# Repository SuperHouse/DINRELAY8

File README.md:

DIN-Mount 8-Channel Relay Output
================================
Copyright 2017-2018 SuperHouse Automation Pty Ltd  www.superhouse.tv  

8-channel relay board designed for switching mains loads in a
switchboard. Fits inside a H8456 DIN-rail mounted case.

Includes a switchmode power supply with 5V output. Controls for the
relays are provided on an I/O Breakout header (12-pin IDC) compatible
with other I/O Breakout boards from SuperHouse.

More information is available at:

  http://www.superhouse.tv/dinrelay8

INSTALLATION
------------
The design is saved as an EAGLE project. EAGLE PCB design software is
available from www.cadsoftusa.com free for non-commercial use. To use
this project download it and place the directory containing these files
into the "eagle" directory on your computer. Then open EAGLE and
navigate to the project.

DISTRIBUTION
------------
The specific terms of distribution of this project are governed by the
license referenced below.

LICENSE
-------
Licensed under the TAPR Open Hardware License (www.tapr.org/OHL).
The "license" folder within this repository also contains a copy of
this license in plain text format.

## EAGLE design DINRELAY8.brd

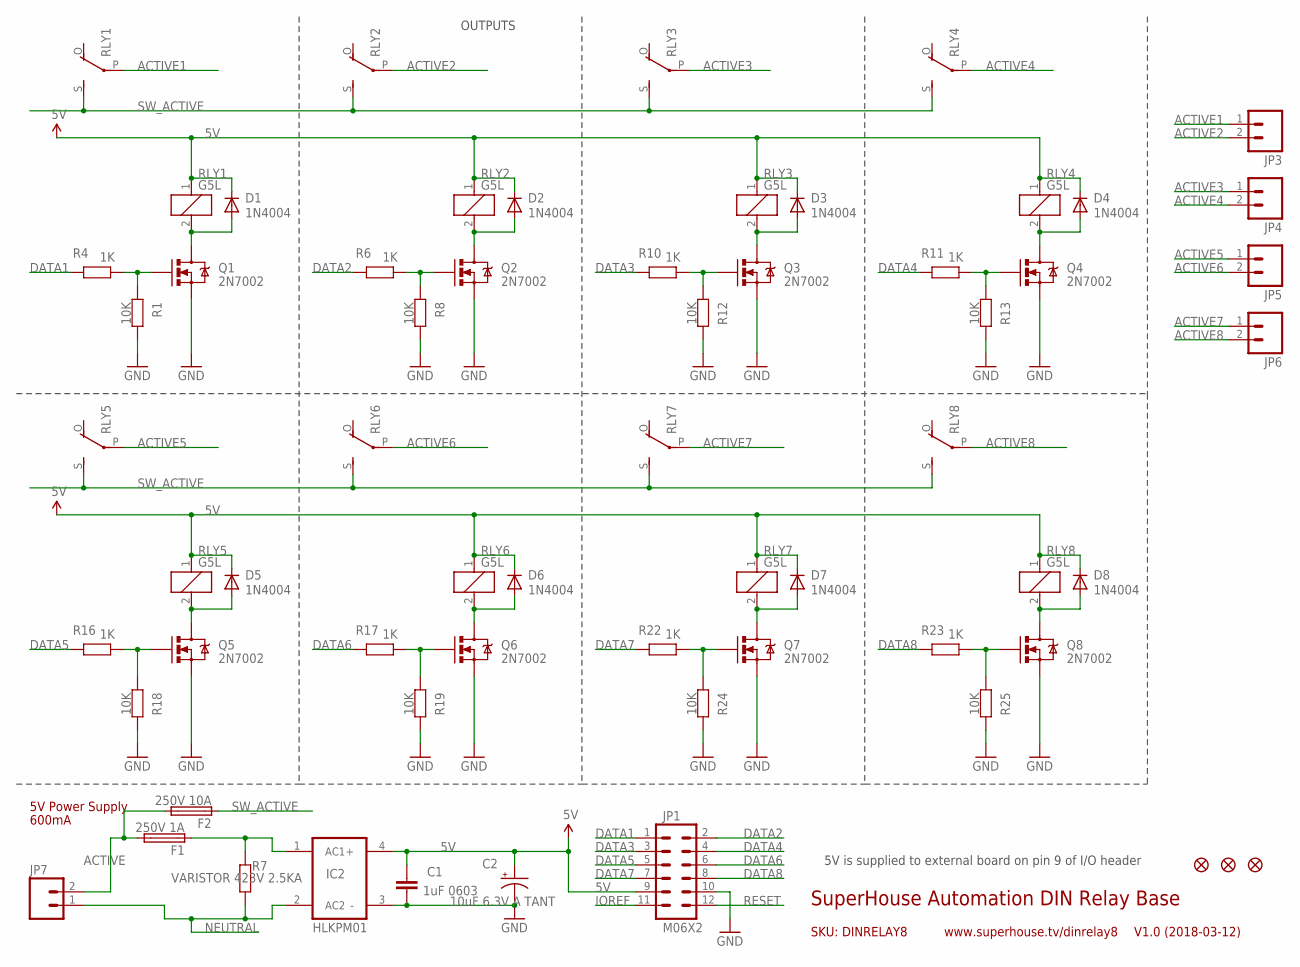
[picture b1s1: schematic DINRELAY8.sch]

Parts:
C1: 1uF 0603; 0603@1
C2: 10uF 6.3V A TANT; EIA3216
D1, D2, D3, D4, D5, D6, D7, D8: 1N4004; SMB-DIODE
F1: 250V 1A; PICOFUSE
F2: 250V 10A; PICOFUSE
FID1, FID2, FID3: FIDUCIAL1X2.5; FIDUCIAL-1X2.5
IC2: HLKPM01
JP1: M06X2; 2X6-SHROUDED
JP3, JP4, JP5, JP6, JP7: M025MM; SCREWTERMINAL-5MM-2
Q1, Q2, Q3, Q4, Q5, Q6, Q7, Q8: 2N7002; SOT23-3
R1, R8, R12, R13, R18, R19, R24, R25: 10K; 0603
R4, R6, R10, R11, R16, R17, R22, R23: 1K; 0603
R7: VARISTOR 423V 2.5KA; AXIAL-0.3
RLY1, RLY2, RLY3, RLY4, RLY5, RLY6, RLY7, RLY8: G5L; G5LE

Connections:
5V: C1.1, C2.A (+), D1.C, D2.C, D3.C, D4.C, D5.C, D6.C, D7.C, D8.C, IC2.4 (+), JP1.9, RLY1.1, RLY2.1, RLY3.1, RLY4.1, RLY5.1, RLY6.1, RLY7.1, RLY8.1
$N16: F1.1, IC2.1 (AC1), R7.P$2 (2)
ACTIVE: F1.2, F2.2, JP7.2
ACTIVE1: JP3.1, RLY1.P
ACTIVE2: JP3.2, RLY2.P
ACTIVE3: JP4.1, RLY3.P
ACTIVE4: JP4.2, RLY4.P
ACTIVE5: JP5.1, RLY5.P
ACTIVE6: JP5.2, RLY6.P
ACTIVE7: JP6.1, RLY7.P
ACTIVE8: JP6.2, RLY8.P
DATA1: JP1.1, R4.2
DATA2: JP1.2, R6.2
DATA3: JP1.3, R10.2
DATA4: JP1.4, R11.2
DATA5: JP1.5, R16.2
DATA6: JP1.6, R17.2
DATA7: JP1.7, R22.2
DATA8: JP1.8, R23.2
GND: C1.2, C2.C (-), IC2.3 (-), JP1.10, Q1.2 (S), Q2.2 (S), Q3.2 (S), Q4.2 (S), Q5.2 (S), Q6.2 (S), Q7.2 (S), Q8.2 (S), R1.2, R8.2, R12.2, R13.2, R18.2, R19.2, R24.2, R25.2
IOREF: JP1.11
unnamed: D2.A, Q2.3 (D), RLY2.2
unnamed: D1.A, Q1.3 (D), RLY1.2
unnamed: Q1.1 (G), R1.1, R4.1
unnamed: Q2.1 (G), R6.1, R8.1
unnamed: D4.A, Q4.3 (D), RLY4.2
unnamed: D3.A, Q3.3 (D), RLY3.2
unnamed: Q3.1 (G), R10.1, R12.1
unnamed: Q4.1 (G), R11.1, R13.1
unnamed: D6.A, Q6.3 (D), RLY6.2
unnamed: D5.A, Q5.3 (D), RLY5.2
unnamed: Q5.1 (G), R16.1, R18.1
unnamed: Q6.1 (G), R17.1, R19.1
unnamed: D8.A, Q8.3 (D), RLY8.2
unnamed: D7.A, Q7.3 (D), RLY7.2
unnamed: Q7.1 (G), R22.1, R24.1
unnamed: Q8.1 (G), R23.1, R25.1
NEUTRAL: IC2.2 (AC2), JP7.1, R7.P$1 (1)
RESET: JP1.12
SW_ACTIVE: F2.1, RLY1.S, RLY2.S, RLY3.S, RLY4.S, RLY5.S, RLY6.S, RLY7.S, RLY8.S

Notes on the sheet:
SKU: DINRELAY8
5V Power Supply
600mA
SuperHouse Automation DIN Relay Base
V1.0 (2018-03-12)
www.superhouse.tv/dinrelay8
OUTPUTS
5V is supplied to external board on pin 9 of I/O header

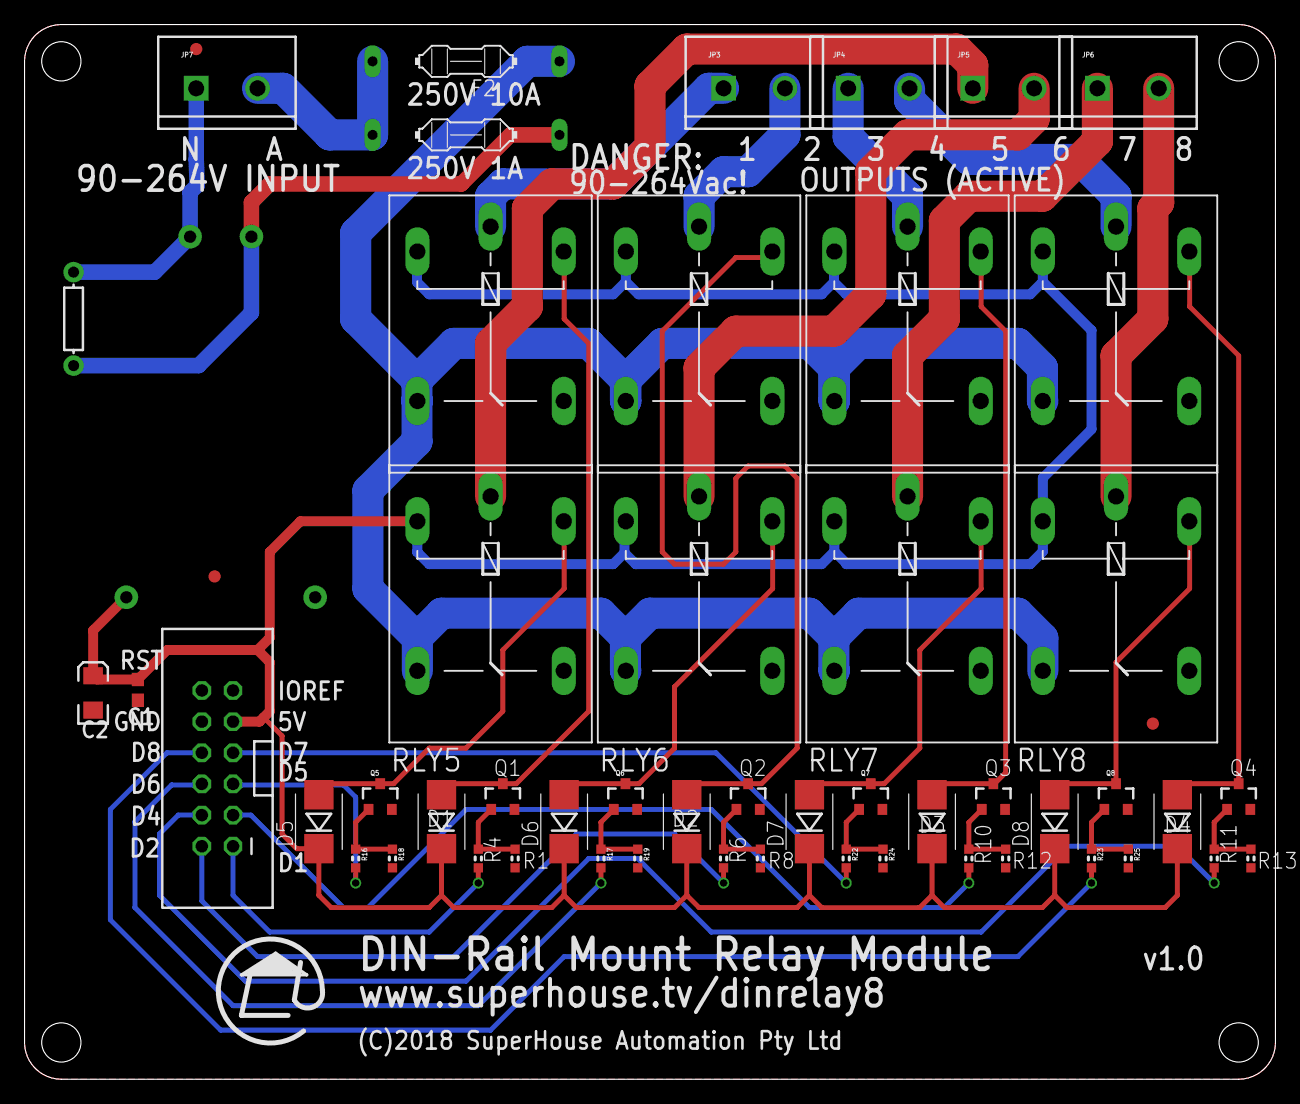
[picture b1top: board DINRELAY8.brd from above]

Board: 2 copper layers, 102.0 x 86.0 mm, 55 parts (0 on the bottom side), 38 nets.

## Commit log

2018-03-28 Initial project import for v1.0 release

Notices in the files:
DINRELAY8.brd:
(C)2018 SuperHouse Automation Pty Ltd
parts and their libraries:
freetronics-original: Licensing: CC v3.0 Share-Alike You are welcome to use this library for commercial purposes.
